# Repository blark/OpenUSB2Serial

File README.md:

# OpenUSB2Serial

An open source USB to serial adapter based on the cheap CH340C IC.

You can get 3 of these boards [from Oshpark](https://oshpark.com/shared_projects/jZ18QKPG) for $5.35.

## BOM

The BOM is [here](/bom.csv) all passives are 805.

Sourcing parts:  
[USB-C connector](https://lcsc.com/product-detail/USB-Type-C_Korean-Hroparts-Elec-TYPE-C-31-M-12_C165948.html)  
[CH340C](https://lcsc.com/product-detail/USB-ICs_WCH-Jiangsu-Qin-Heng-CH340C_C84681.html)  
[AZ1117-3.3](https://lcsc.com/product-detail/Low-Dropout-Regulators-LDO_Diodes-Incorporated-AZ1117CH-3-3TRG1_C92102.html)

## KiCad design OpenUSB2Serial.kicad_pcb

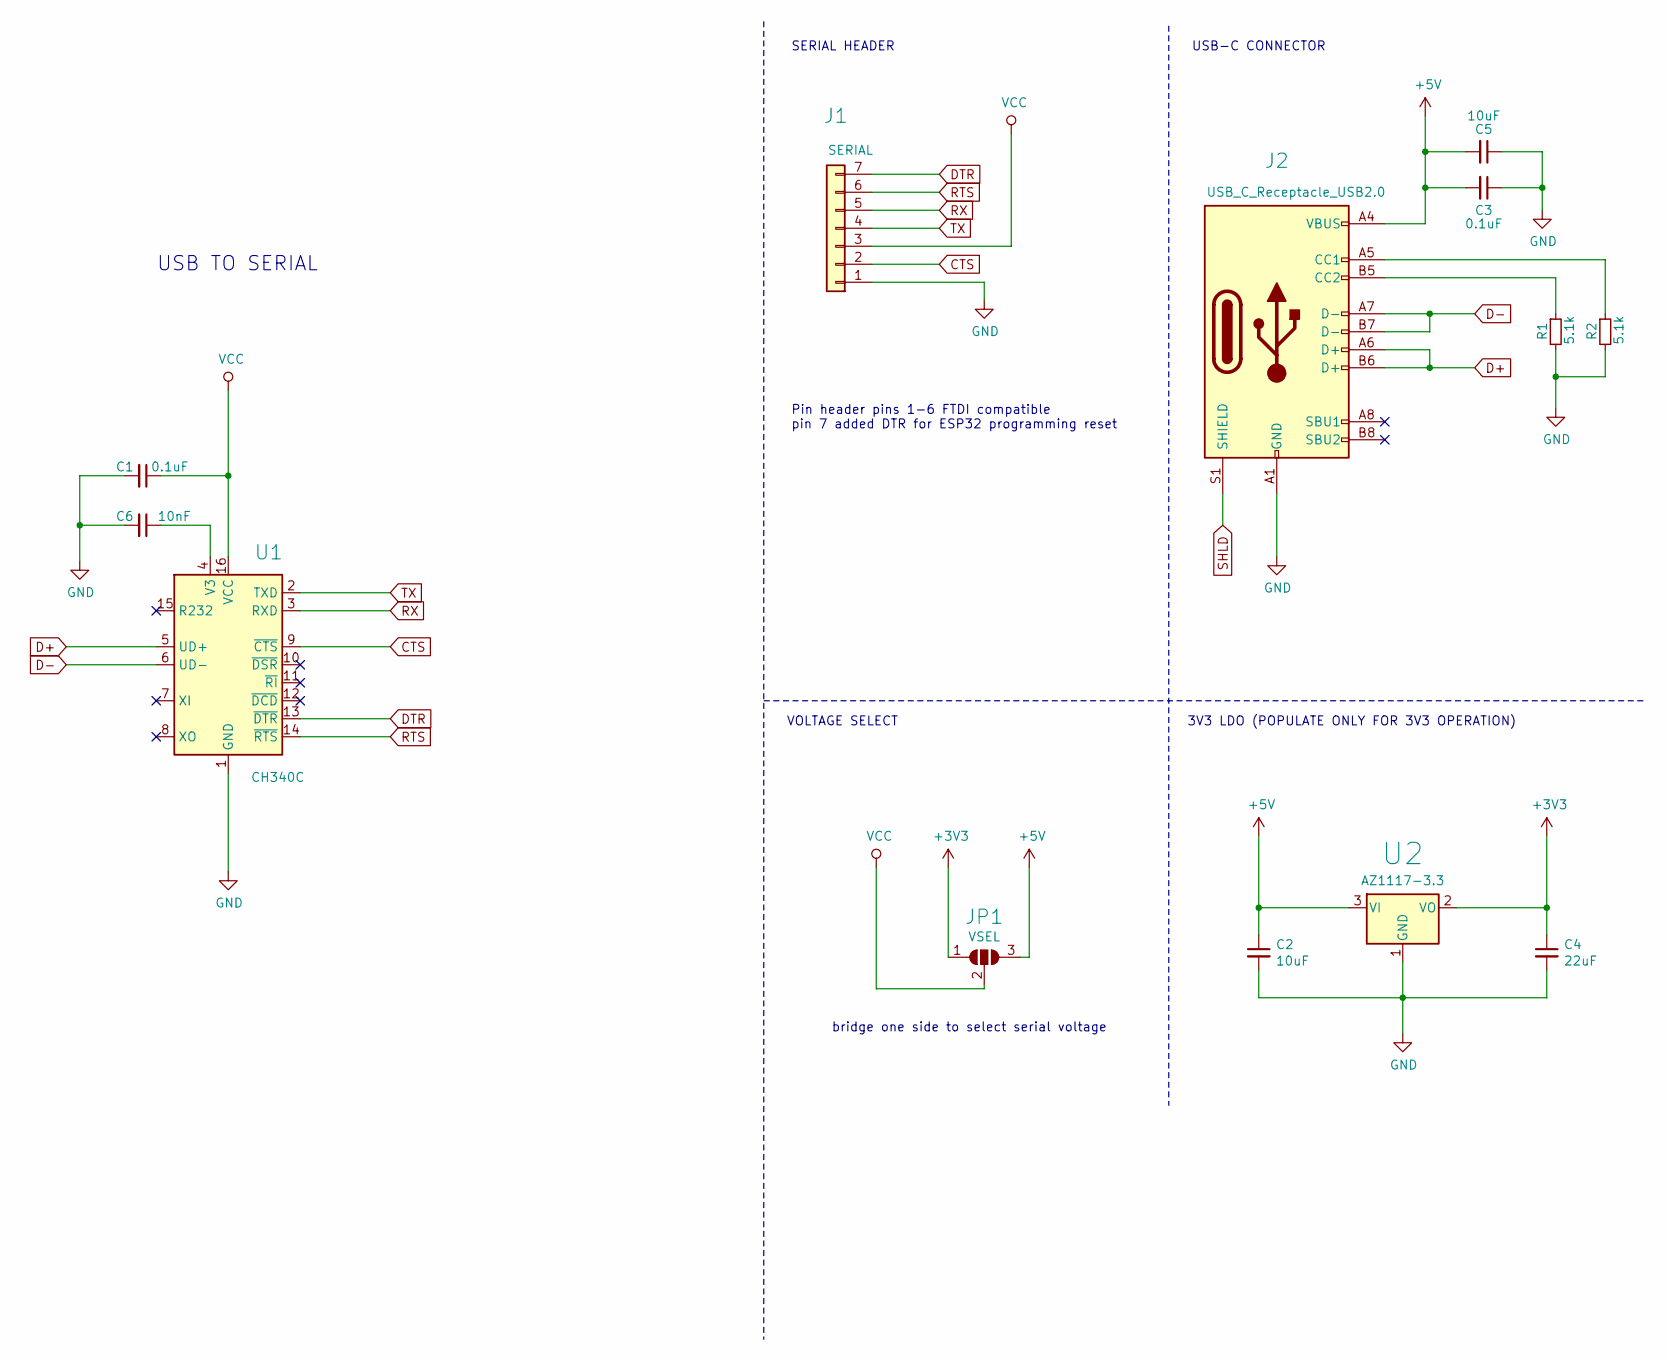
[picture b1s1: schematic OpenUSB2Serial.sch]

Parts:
C1, C3: 0.1uF; C_0805_2012Metric
C2, C5: 10uF; C_0805_2012Metric
C4: 22uF; C_0805_2012Metric
C6: 10nF; C_0805_2012Metric
J1: SERIAL; PinHeader_1x07_P2.54mm_Vertical
J2: USB_C_Receptacle_USB2.0; USB_C_Receptacle_HRO_TYPE-C-31-M-12
JP1: VSEL; SolderJumper-3_P2.0mm_Open_TrianglePad1.0x1.5mm
R1, R2: 5.1k; R_0805_2012Metric
U1: CH340C; SOIC-16_3.9x9.9mm_P1.27mm
U2: AZ1117-3.3; SOT-223

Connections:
+3V3: C4.1, JP1.1 (A), U2.2 (VO)
+5V: C2.1, C3.2, C5.2, J2.A4 (VBUS), J2.A9 (VBUS), J2.B4 (VBUS), J2.B9 (VBUS), JP1.3 (B), U2.3 (VI)
CTS: J1.2, U1.9 (~CTS)
D+: J2.A6 (D+), J2.B6 (D+), U1.5 (UD+)
D-: J2.A7 (D-), J2.B7 (D-), U1.6 (UD-)
DTR: J1.7, U1.13 (~DTR)
GND: C1.2, C2.2, C3.1, C4.2, C5.1, C6.2, J1.1, J2.A1 (GND), J2.A12 (GND), J2.B1 (GND), J2.B12 (GND), R1.2, R2.2, U1.1 (GND), U2.1 (GND)
unnamed: C6.1, U1.4 (V3)
unnamed: J2.A5 (CC1), R2.1
unnamed: J2.B5 (CC2), R1.1
RTS: J1.6, U1.14 (~RTS)
RX: J1.5, U1.3 (RXD)
SHLD: J2.S1 (SHIELD)
TX: J1.4, U1.2 (TXD)
VCC: C1.1, J1.3, JP1.2 (C), U1.16 (VCC)

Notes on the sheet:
3V3 LDO (POPULATE ONLY FOR 3V3 OPERATION)
USB-C CONNECTOR
USB TO SERIAL
Pin header pins 1-6 FTDI compatible pin 7 added DTR for ESP32 programming reset
SERIAL HEADER
VOLTAGE SELECT
bridge one side to select serial voltage

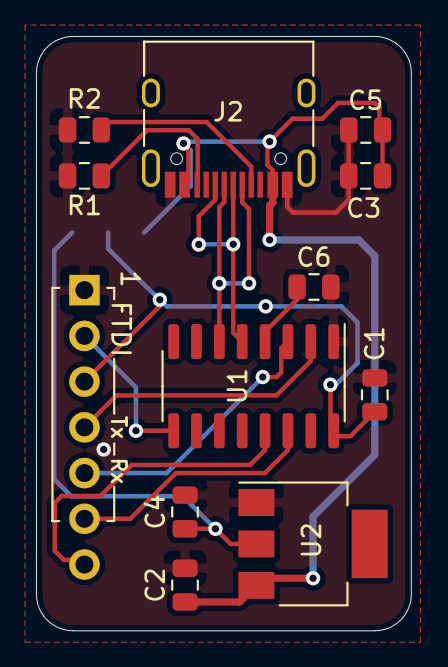
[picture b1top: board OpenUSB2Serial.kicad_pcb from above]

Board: 2 copper layers, 20.8 x 33.0 mm, 13 parts (1 on the bottom side), 14 nets.

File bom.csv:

"Ref","Qnty","Value","Cmp name","Footprint","Description","Vendor"
"C1, C3, ","2","0.1uF","C_Small","Capacitor_SMD:C_0805_2012Metric","Unpolarized capacitor, small symbol",""
"C2, C5, ","2","10uF","C_Small","Capacitor_SMD:C_0805_2012Metric","Unpolarized capacitor, small symbol",""
"C4, ","1","22uF","C_Small","Capacitor_SMD:C_0805_2012Metric","Unpolarized capacitor, small symbol",""
"C6, ","1","10nF","C_Small","Capacitor_SMD:C_0805_2012Metric","Unpolarized capacitor, small symbol",""
"J1, ","1","SERIAL","Conn_01x07","Connector_PinHeader_2.54mm:PinHeader_1x07_P2.54mm_Vertical","Generic connector, single row, 01x07, script generated (kicad-library-utils/schlib/autogen/connector/)",""
"J2, ","1","USB_C_Receptacle_USB2.0","USB_C_Receptacle_USB2.0","Connector_USB:USB_C_Receptacle_HRO_TYPE-C-31-M-12","USB 2.0-only Type-C Receptacle connector",""
"JP1, ","1","VSEL","SolderJumper_3_Open","Jumper:SolderJumper-3_P2.0mm_Open_TrianglePad1.0x1.5mm","Solder Jumper, 3-pole, open",""
"R1, R2, ","2","5.1k","R_Small","Resistor_SMD:R_0805_2012Metric","Resistor, small symbol",""
"U1, ","1","CH340C","CH340G","Package_SO:SOIC-16_3.9x9.9mm_P1.27mm","USB serial converter, UART, SOIC-16",""
"U2, ","1","AZ1117-3.3","AZ1117-3.3","Package_TO_SOT_SMD:SOT-223","1A 20V Fixed LDO Linear Regulator, 3.3V, SOT-89/SOT-223/TO-220/TO-252/TO-263",""

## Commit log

2020-06-01 bom stuff
2020-06-01 fix osh link
